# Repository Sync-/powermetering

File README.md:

# powermetering
```
ADE9000 application circuit based power meter
default ip: 192.168.178.204
st-flash --reset write build/powermetering.bin 0x08020000
```

Building:
```
cd software/website
./makefsdata
./copy.sh

cd software/powermetering
make
```

Flashing:
```
socat TCP:192.168.178.204:2000 build/powermetering.bin
```

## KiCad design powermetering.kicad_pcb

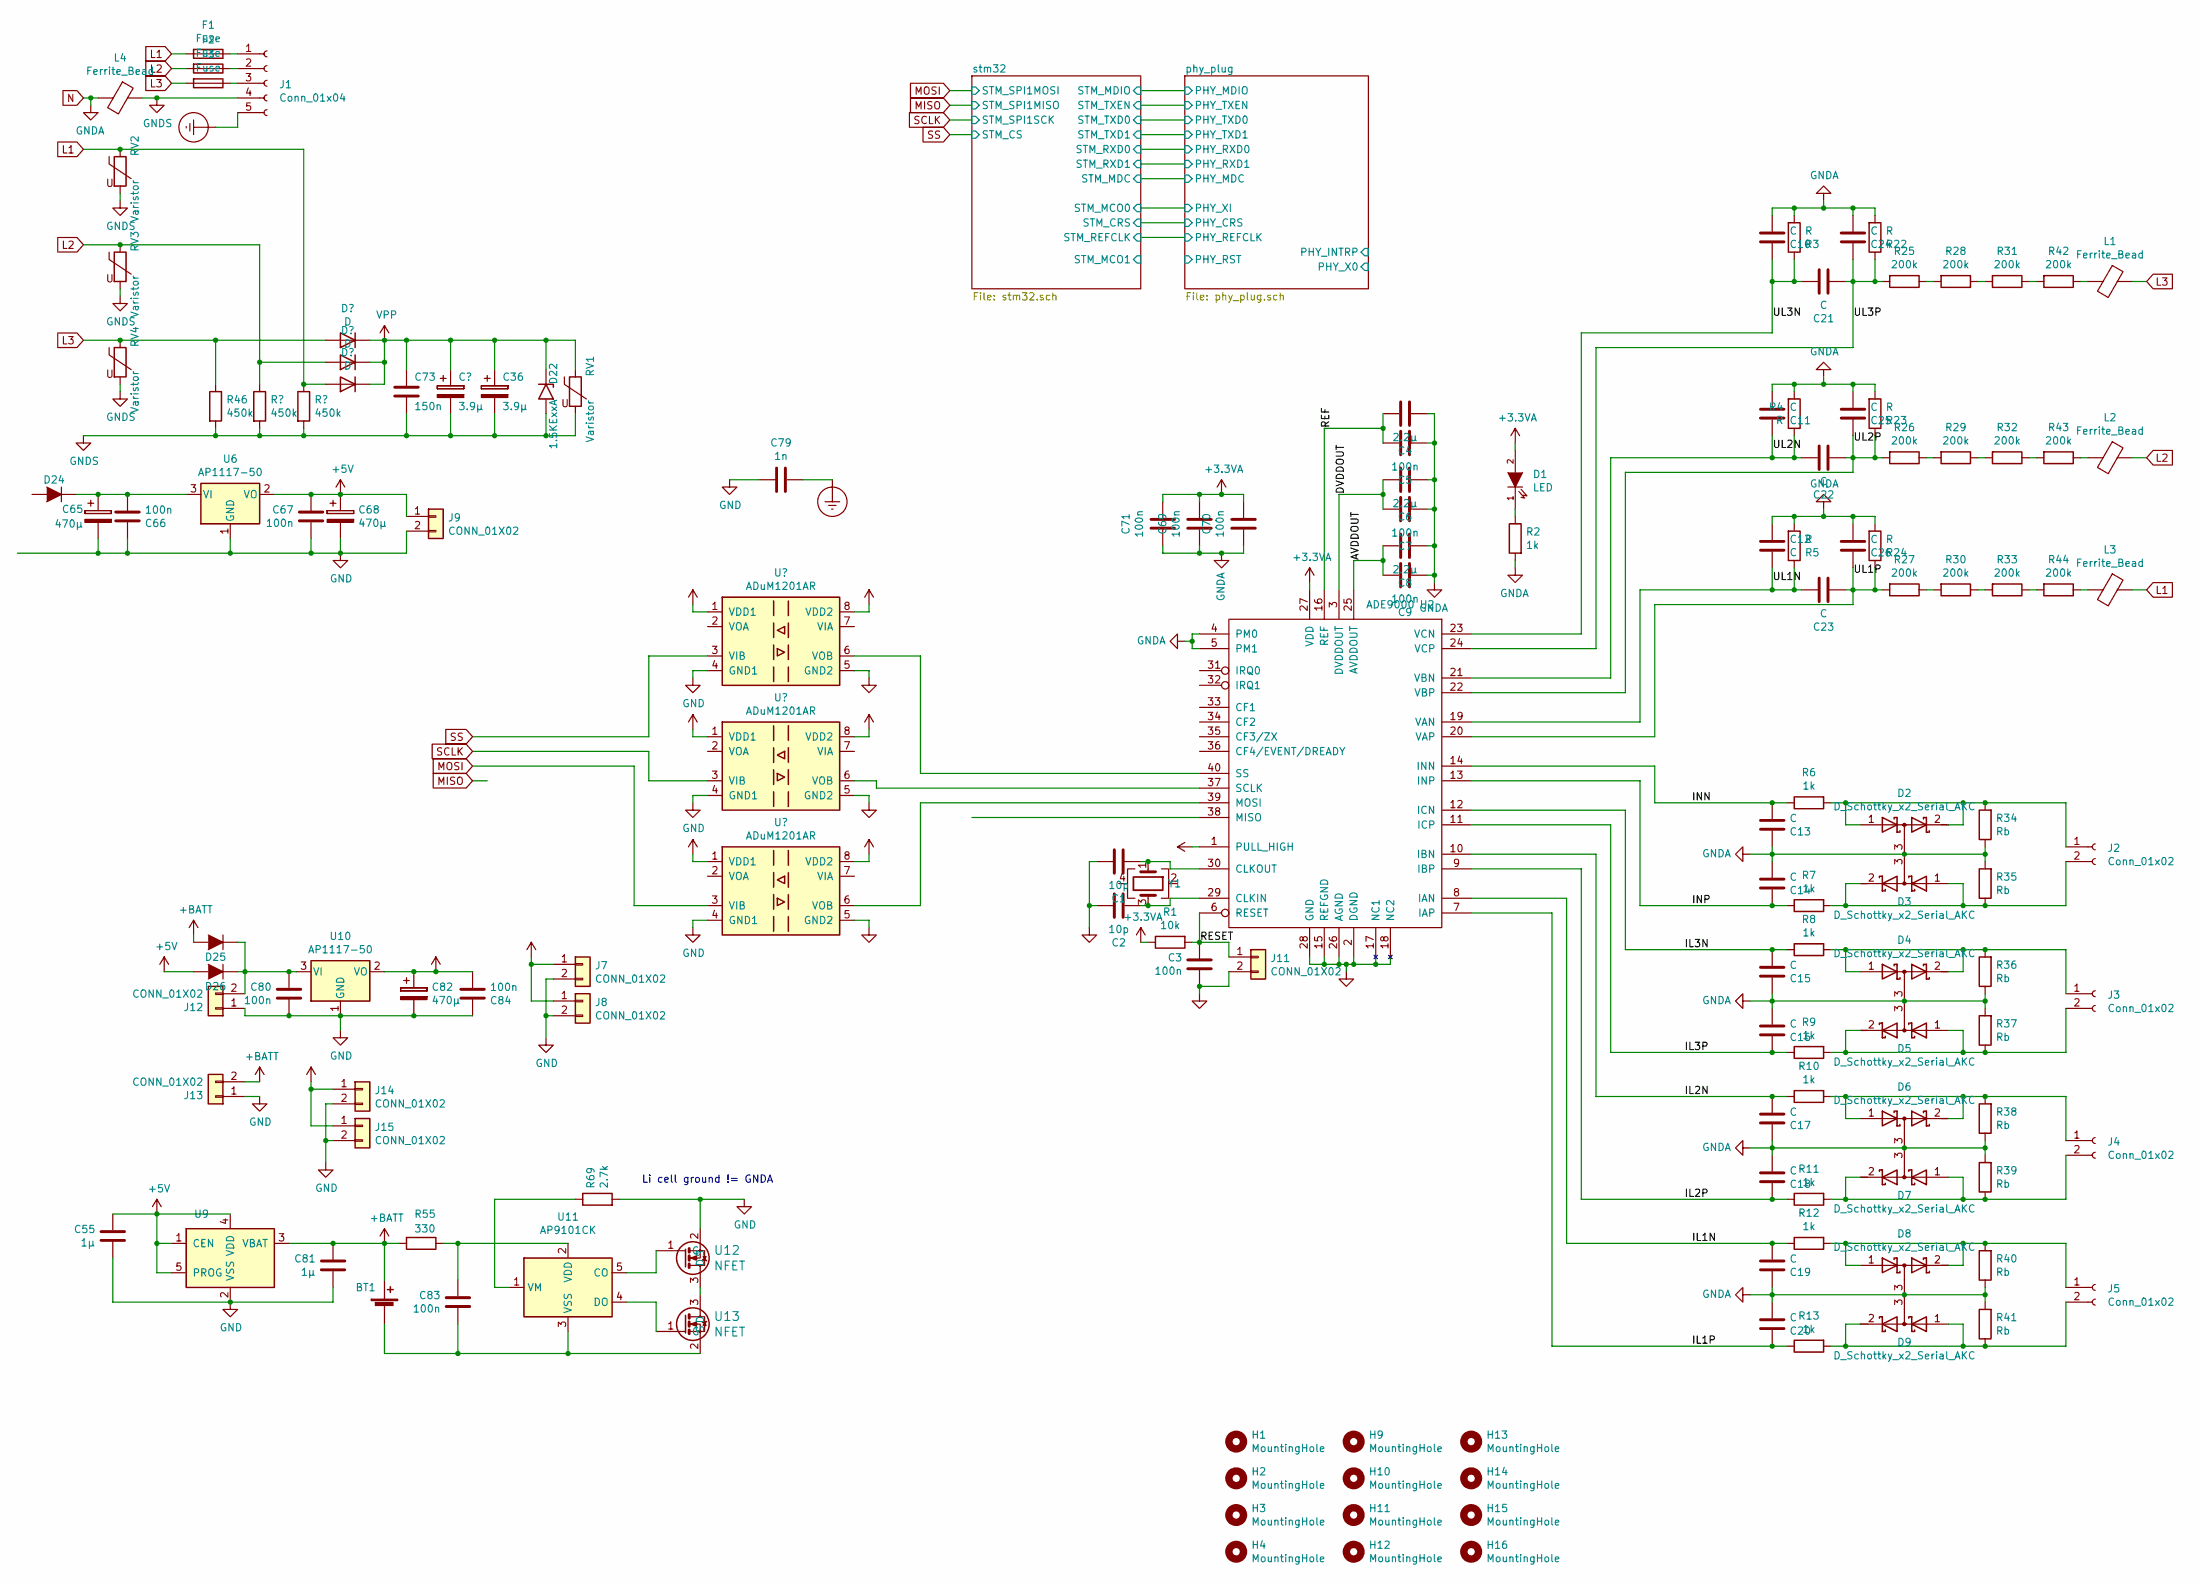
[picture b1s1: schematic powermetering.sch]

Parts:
BT1: Battery_Cell; 18650_keystone_54
C1, C2: 10p; C_0603
C3, C5, C7, C9, C69, C70, C71: 100n; C_0603
C4, C6, C8: 2.2µ; C_0603
C10, C11, C12, C13, C14, C15, C16, C17, C18, C19, C20, C21, C22, C23, C24, C25, C26: C; C_0603
C36: 3.9µ; CP_Elec_8x10
C55, C81: 1µ; C_0805
C65: 470µ; CP_Elec_8x10
C66, C67, C80, C83, C84: 100n; C_0805
C68, C82: 470µ; CP_Elec_8x10.5
C73: 150n; C_1808
C79: 1n; C_1806_4516Metric
D1: LED; LED-0805
D2, D3, D4, D5, D6, D7, D8, D9: D_Schottky_x2_Serial_AKC; SOT-23
D22: 1.5KExxA; D_SMC
D24, D25, D26: D; SMA_Standard
F1, F2, F3: Fuse; Fuse_SunFuse-6HP
H1, H2, H3, H4, H9, H10, H11, H12, H13, H14, H15, H16: MountingHole; MountingHole_5.5mm
J1: Conn_01x04; RM5.08_1x5_UP
J2, J3, J4, J5: Conn_01x02; RM5.08_1x2_UP
J7, J8, J9, J11, J12, J13, J14, J15: CONN_01X02; Pin_Header_Straight_1x02
L1, L2, L3, L4: Ferrite_Bead; C_0805
R1: 10k; R_0603
R2, R6, R7, R8, R9, R10, R11, R12, R13: 1k; R_0603
R3, R4, R5, R22, R23, R24: R; R_0603
R25, R26, R27, R28, R29, R30, R31, R32, R33, R42, R43, R44: 200k; R_1206
R34, R35, R36, R37, R38, R39, R40, R41: Rb; R_0612_1632Metric
R46: 450k; R_1206
R55: 330; R_0805
R69: 2.7k; R_0805
RV1, RV2, RV3, RV4: Varistor; RV_Disc_D12mm_W3.9mm_P7.5mm
U2: ADE9000; QFN-40-1EP_6x6mm_Pitch0.5mm
U6, U10: AP1117-50; SOT-223-3_TabPin2
U9: MCP73811T-420I-OT; SOT-23-5
U11: AP9101CK; SOT-23-5
U12, U13: NFET; SOT-23
Y1: Crystal; Crystal_SMD_3225-4Pin_3.2x2.5mm

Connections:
+3.3VA: C69.2, C70.2, C71.2, D1.2 (A), R1.1, U2.1 (PULL_HIGH), U2.27 (VDD); also elsewhere on the board
+3V3: C82.1, C84.2, J7.1, J8.1, J14.1, J15.1, U10.2 (VO); also elsewhere on the board
+5V: C55.1, C67.1, C68.1, D26.2 (A), J9.1, U6.2 (VO), U9.1 (CEN), U9.4 (VDD), U9.5 (PROG)
+BATT: BT1.1 (+), C81.1, D25.2 (A), J13.2, R55.2, U9.3 (VBAT)
/AVDDOUT: C8.2, C9.2, U2.25 (AVDDOUT)
/DVDDOUT: C6.2, C7.2, U2.3 (DVDDOUT)
/IL1N: C19.1, R12.1, U2.8 (IAN)
/IL1P: C20.2, R13.1, U2.7 (IAP)
/IL2N: C17.1, R10.1, U2.10 (IBN)
/IL2P: C18.2, R11.1, U2.9 (IBP)
/IL3N: C15.1, R8.1, U2.12 (ICN)
/IL3P: C16.2, R9.1, U2.11 (ICP)
/INN: C13.1, R6.1, U2.14 (INN)
/INP: C14.2, R7.1, U2.13 (INP)
/REF: C4.2, C5.2, U2.16 (REF)
/RESET: C3.2, J11.1, R1.2, U2.6 (RESET)
/UL1N: C12.2, C23.2, R5.1, U2.19 (VAN)
/UL1P: C23.1, C26.2, R24.1, R27.2, U2.20 (VAP)
/UL2N: C11.2, C22.2, R4.1, U2.21 (VBN)
/UL2P: C22.1, C25.2, R23.1, R26.2, U2.22 (VBP)
/UL3N: C10.2, C21.2, R3.1, U2.23 (VCN)
/UL3P: C21.1, C24.2, R22.1, R25.2, U2.24 (VCP)
Earth_Protective: C79.2, J1.5
GND: C55.2, C65.2, C66.1, C67.2, C68.2, C79.1, C80.2, C81.2, C82.2, C84.1, J7.2, J8.2, J9.2, J12.1, J13.1, J14.2, J15.2, R69.2, U6.1 (GND), U9.2 (VSS), U10.1 (GND), U12.2 (S); also elsewhere on the board
L1: F1.2, L3.1, RV2.1; also elsewhere on the board
L2: F2.2, L2.1, RV3.1; also elsewhere on the board
N: C1.2, C2.2, C3.1, C4.1, C5.1, C6.1, C7.1, C8.1, C9.1, C10.1, C11.1, C12.1, C13.2, C14.1, C15.2, C16.1, C17.2, C18.1, C19.2, C20.1, C24.1, C25.1, C26.1, C69.1, C70.1, C71.1, D2.3 (common), D3.3 (common), D4.3 (common), D5.3 (common), D6.3 (common), D7.3 (common), D8.3 (common), D9.3 (common), J11.2, L4.2, R2.2, R3.2, R4.2, R5.2, R22.2, R23.2, R24.2, R34.1, R35.2, R36.1, R37.2, R38.1, R39.2, R40.1, R41.2, U2.2 (DGND), U2.4 (PM0), U2.5 (PM1), U2.15 (REFGND), U2.17 (NC1), U2.18 (NC2), U2.26 (AGND), U2.28 (GND); also elsewhere on the board
unnamed: BT1.2 (-), C83.2, U11.3 (VSS), U13.2 (S)
unnamed: C1.1, U2.30 (CLKOUT), Y1.1
unnamed: C2.1, U2.29 (CLKIN), Y1.3
unnamed: C65.1, C66.2, D24.1 (K), U6.3 (VI)
unnamed: C80.1, D25.1 (K), D26.1 (K), J12.2, U10.3 (VI)
unnamed: C83.1, R55.1, U11.2 (VDD)
unnamed: D1.1 (K), R2.1
unnamed: D2.1 (A), D2.2 (K), J2.1, R6.2, R34.2
unnamed: D3.1 (A), D3.2 (K), J2.2, R7.2, R35.1
unnamed: D4.1 (A), D4.2 (K), J3.1, R8.2, R36.2
unnamed: D5.1 (A), D5.2 (K), J3.2, R9.2, R37.1
unnamed: D6.1 (A), D6.2 (K), J4.1, R10.2, R38.2
unnamed: D7.1 (A), D7.2 (K), J4.2, R11.2, R39.1
unnamed: D8.1 (A), D8.2 (K), J5.1, R12.2, R40.2
unnamed: D9.1 (A), D9.2 (K), J5.2, R13.2, R41.1
unnamed: F1.1, J1.1
unnamed: F2.1, J1.2
unnamed: F3.1, J1.3
unnamed: L1.2, R42.1
unnamed: L2.2, R43.1
unnamed: L3.2, R44.1
unnamed: R25.1, R28.2
unnamed: R26.1, R29.2
unnamed: R27.1, R30.2
unnamed: R28.1, R31.2
unnamed: R29.1, R32.2
unnamed: R30.1, R33.2
unnamed: R31.1, R42.2
unnamed: R32.1, R43.2
unnamed: R33.1, R44.2
unnamed: R69.1, U11.1 (VM)
unnamed 160: U2.37 (SCLK); also elsewhere on the board
unnamed 161: U2.38 (MISO); also elsewhere on the board
unnamed 162: U2.39 (MOSI); also elsewhere on the board
unnamed 163: U2.40 (SS); also elsewhere on the board
unnamed: U11.4 (DO), U13.1 (G)
unnamed: U11.5 (CO), U12.1 (G)
unnamed: U12.3 (D), U13.3 (D)

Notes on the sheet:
Li cell ground != GNDA

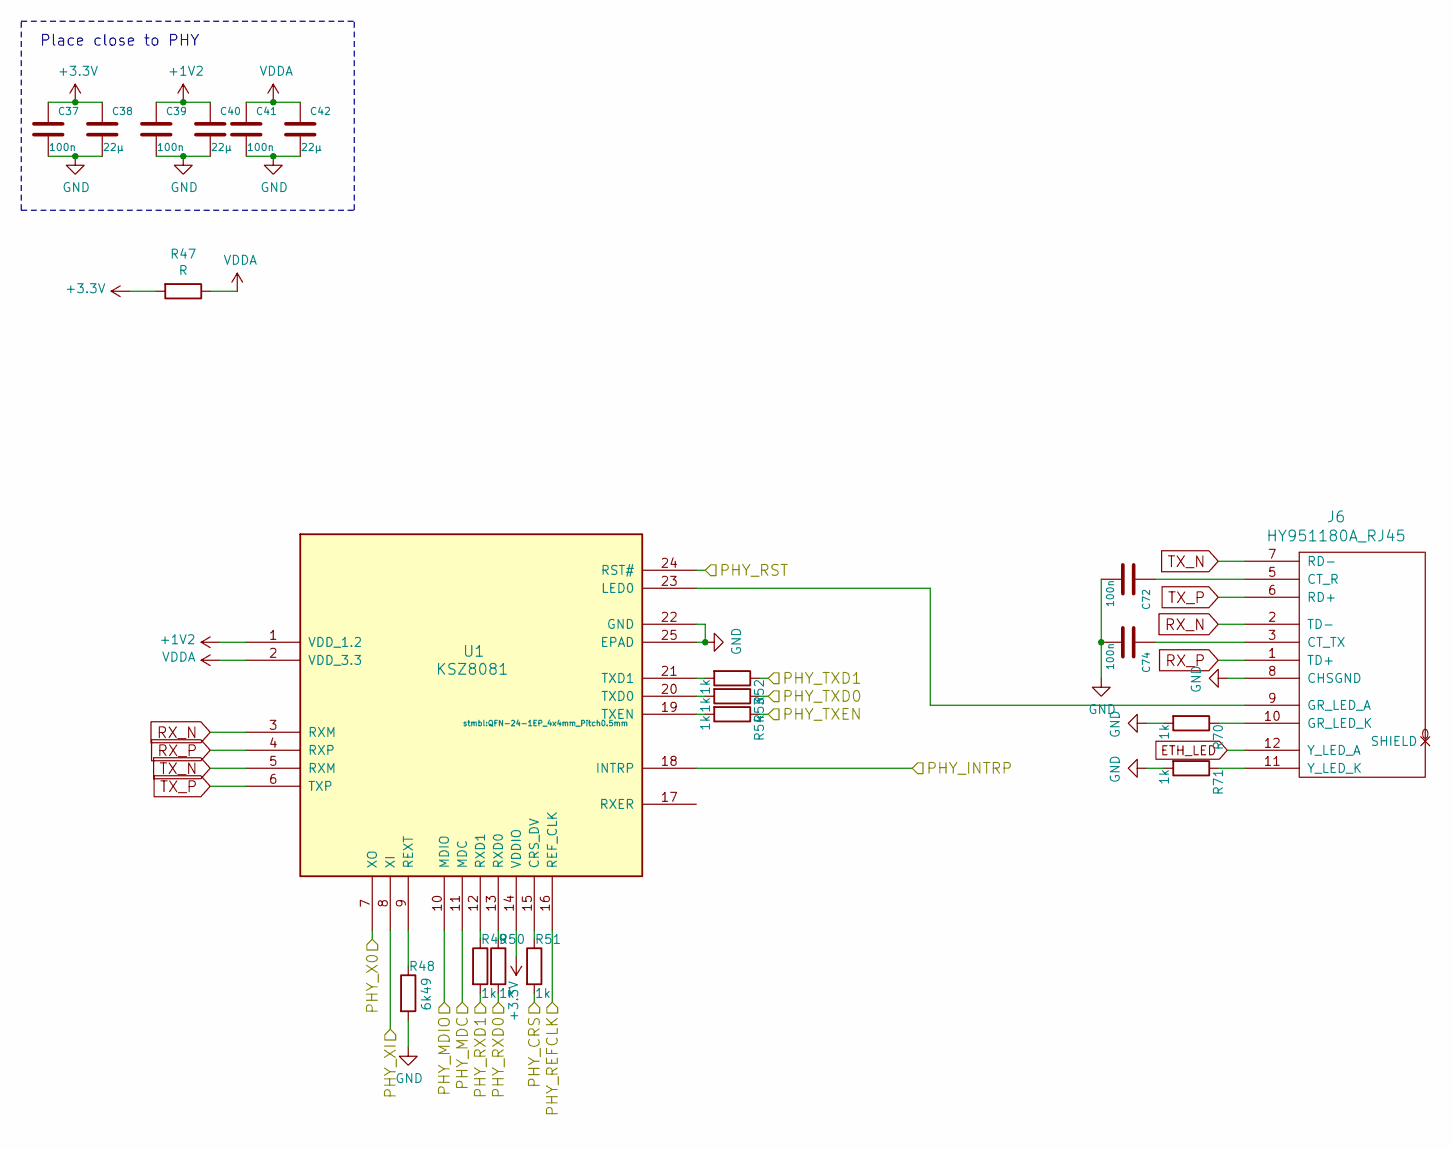
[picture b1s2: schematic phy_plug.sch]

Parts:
C37, C39, C41, C72, C74: 100n; C_0603
C38, C40, C42: 22µ; C_0805
J6: HY951180A_RJ45
R47: R; R_0603
R48: 6k49; R_0603
R49, R50, R51, R52, R53, R54, R70, R71: 1k; R_0603
U1: KSZ8081; QFN-24-1EP_4x4mm_Pitch0.5mm

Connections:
+1V2: C39.1, C40.1, U1.1 (VDD_1.2)
+3V3: C37.1, C38.1, R47.2, U1.14 (VDDIO); also elsewhere on the board
/PHY_CRS: R51.2; also elsewhere on the board
/PHY_INTRP: U1.18 (INTRP)
/PHY_MDIO: U1.10 (MDIO); also elsewhere on the board
/PHY_RST: U1.24 (RST#)
/PHY_TXD0: R53.1; also elsewhere on the board
/PHY_X0: U1.7 (XO)
/PHY_XI: U1.8 (XI); also elsewhere on the board
/STM_MDC: U1.11 (MDC); also elsewhere on the board
/STM_REFCLK: U1.16 (REF_CLK); also elsewhere on the board
/STM_RXD0: R50.2; also elsewhere on the board
/STM_RXD1: R49.2; also elsewhere on the board
/STM_TXD1: R52.1; also elsewhere on the board
/STM_TXEN: R54.1; also elsewhere on the board
ETH_LED: J6.12 (Y_LED_A); also elsewhere on the board
GND: C37.2, C38.2, C39.2, C40.2, C41.2, C42.2, C72.2, C74.2, J6.8 (CHSGND), R48.2, R70.2, R71.2, U1.22 (GND), U1.25 (EPAD); also elsewhere on the board
unnamed: C72.1, J6.5 (CT_R)
unnamed: C74.1, J6.3 (CT_TX)
unnamed: J6.9 (GR_LED_A), U1.23 (LED0)
unnamed: J6.10 (GR_LED_K), R70.1
unnamed: J6.11 (Y_LED_K), R71.1
unnamed: R48.1, U1.9 (REXT)
unnamed: R49.1, U1.12 (RXD1)
unnamed: R50.1, U1.13 (RXD0)
unnamed: R51.1, U1.15 (CRS_DV)
unnamed: R52.2, U1.21 (TXD1)
unnamed: R53.2, U1.20 (TXD0)
unnamed: R54.2, U1.19 (TXEN)
RX_N: J6.2 (TD-), U1.3 (RXM)
RX_P: J6.1 (TD+), U1.4 (RXP)
TX_N: J6.7 (RD-), U1.5 (RXM)
TX_P: J6.6 (RD+), U1.6 (TXP)
VDDA: C41.1, C42.1, R47.1, U1.2 (VDD_3.3)

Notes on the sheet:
Place close to PHY

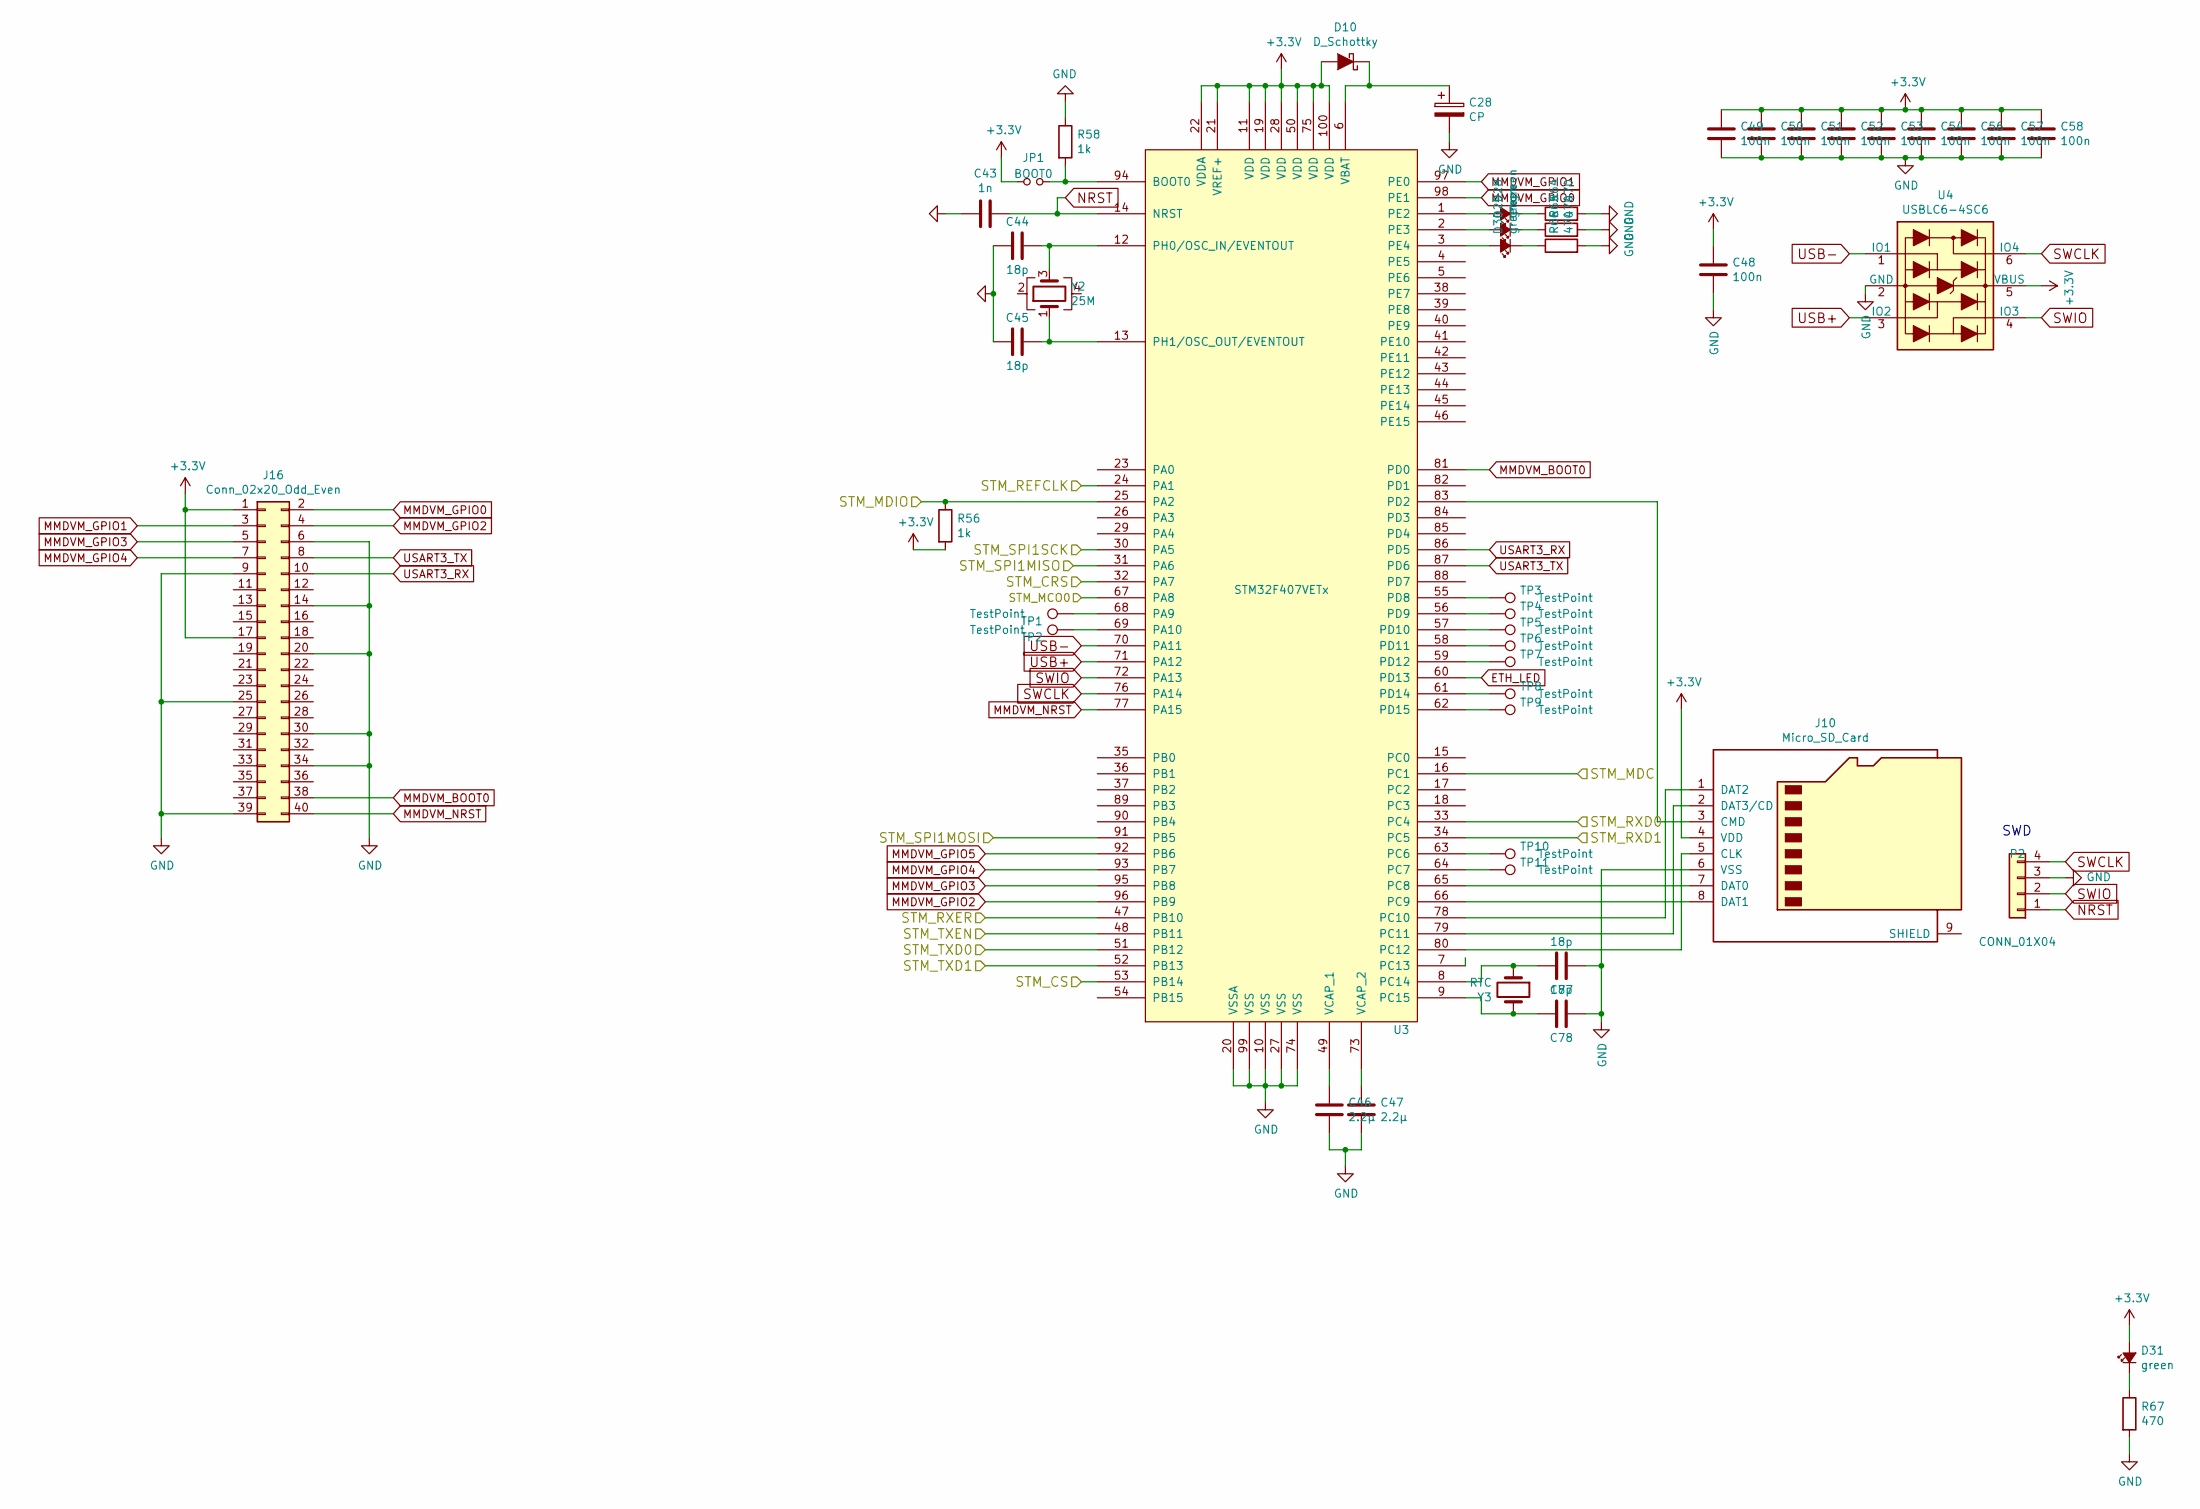
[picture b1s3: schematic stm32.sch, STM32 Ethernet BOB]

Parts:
C28: CP
C43: 1n; C_0603; Tolerance X5R; Voltage 50V
C44, C45, C77, C78: 18p; C_0603; Tolerance X5R; Voltage 50V
C46, C47: 2.2µ; C_0603; Tolerance X5R; Voltage 25V
C48, C49, C50, C51, C52, C53, C54, C56, C57, C58: 100n; C_0603; Tolerance X5R; Voltage 50V
D10: D_Schottky
D28, D29, D30, D31: green; LED-0805
J10: Micro_SD_Card; microSD_HC_Hirose_DM3BT-DSF-PEJS
J16: Conn_02x20_Odd_Even; PinHeader_2x20_P2.54mm_Vertical
JP1: BOOT0; SOLDER_JUMPER
P2: CONN_01X04; Pin_Header_Straight_1x04
R56, R58: 1k; R_0603; Tolerance 1%
R64, R65, R66, R67: 470; R_0603; Tolerance 1%
TP1, TP2, TP3, TP4, TP5, TP6, TP7, TP8, TP9, TP10, TP11: TestPoint; TestPoint_Pad_D1.0mm
U3: STM32F407VETx; LQFP-100_14x14mm_Pitch0.5mm
U4: USBLC6-4SC6; SOT-23-6
Y2: 25M; Crystal_SMD_3225-4Pin_3.2x2.5mm
Y3: RTC; Crystal_SMD_3215-2Pin_3.2x1.5mm

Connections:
+3V3: C48.2, C49.2, C50.2, C51.2, C52.2, C53.2, C54.2, C56.2, C57.2, C58.2, D10.2 (A), D31.2 (A), J10.4 (VDD), J16.1, J16.17, JP1.2, R56.2, U3.11 (VDD), U3.19 (VDD), U3.21 (VREF+), U3.22 (VDDA), U3.28 (VDD), U3.50 (VDD), U3.75 (VDD), U3.100 (VDD), U4.5 (VBUS); also elsewhere on the board
/PHY_CRS: U3.32 (PA7); also elsewhere on the board
/PHY_MDIO: R56.1, U3.25 (PA2); also elsewhere on the board
/PHY_TXD0: U3.51 (PB12); also elsewhere on the board
/PHY_XI: U3.67 (PA8); also elsewhere on the board
/STM_MDC: U3.16 (PC1); also elsewhere on the board
/STM_REFCLK: U3.24 (PA1); also elsewhere on the board
/STM_RXD0: U3.33 (PC4); also elsewhere on the board
/STM_RXD1: U3.34 (PC5); also elsewhere on the board
/STM_TXD1: U3.52 (PB13); also elsewhere on the board
/STM_TXEN: U3.48 (PB11); also elsewhere on the board
/stm32/STM_RXER: U3.47 (PB10)
ETH_LED: U3.60 (PD13); also elsewhere on the board
GND: C28.2, C43.2, C44.2, C45.2, C46.1, C47.1, C48.1, C49.1, C50.1, C51.1, C52.1, C53.1, C54.1, C56.1, C57.1, C58.1, C77.2, C78.2, J10.6 (VSS), J16.6, J16.9, J16.14, J16.20, J16.25, J16.30, J16.34, J16.39, P2.3, R58.1, R64.2, R65.2, R66.2, R67.2, U3.10 (VSS), U3.20 (VSSA), U3.27 (VSS), U3.74 (VSS), U3.99 (VSS), U4.2 (GND); also elsewhere on the board
MISO: U3.31 (PA6); also elsewhere on the board
MMDVM_BOOT0: J16.38, U3.81 (PD0)
MMDVM_GPIO0: J16.2, U3.98 (PE1)
MMDVM_GPIO1: J16.3, U3.97 (PE0)
MMDVM_GPIO2: J16.4, U3.96 (PB9)
MMDVM_GPIO3: J16.5, U3.95 (PB8)
MMDVM_GPIO4: J16.7, U3.93 (PB7)
MMDVM_GPIO5: U3.92 (PB6)
MMDVM_NRST: J16.40, U3.77 (PA15)
MOSI: U3.91 (PB5); also elsewhere on the board
NRST: C43.1, P2.1, U3.14 (NRST)
unnamed: C28.1, D10.1 (K), U3.6 (VBAT)
unnamed: C44.1, U3.12 (PH0/OSC_IN/EVENTOUT), Y2.3
unnamed: C45.1, U3.13 (PH1/OSC_OUT/EVENTOUT), Y2.1
unnamed: C46.2, U3.49 (VCAP_1)
unnamed: C47.2, U3.73 (VCAP_2)
unnamed: C77.1, U3.8 (PC14), Y3.1
unnamed: C78.1, U3.9 (PC15), Y3.2
unnamed: D28.1 (K), R64.1
unnamed: D28.2 (A), U3.1 (PE2)
unnamed: D29.1 (K), R65.1
unnamed: D29.2 (A), U3.2 (PE3)
unnamed: D30.1 (K), R66.1
unnamed: D30.2 (A), U3.3 (PE4)
unnamed: D31.1 (K), R67.1
unnamed: J10.1 (DAT2), U3.78 (PC10)
unnamed: J10.2 (DAT3/CD), U3.79 (PC11)
unnamed: J10.3 (CMD), U3.83 (PD2)
unnamed: J10.5 (CLK), U3.80 (PC12)
unnamed: J10.7 (DAT0), U3.65 (PC8)
unnamed: J10.8 (DAT1), U3.66 (PC9)
unnamed: JP1.1, R58.2, U3.94 (BOOT0)
unnamed: TP1.1, U3.68 (PA9)
unnamed: TP2.1, U3.69 (PA10)
unnamed: TP3.1, U3.55 (PD8)
unnamed: TP4.1, U3.56 (PD9)
unnamed: TP5.1, U3.57 (PD10)
unnamed: TP6.1, U3.58 (PD11)
unnamed: TP7.1, U3.59 (PD12)
unnamed: TP8.1, U3.61 (PD14)
unnamed: TP9.1, U3.62 (PD15)
unnamed: TP10.1, U3.63 (PC6)
unnamed: TP11.1, U3.64 (PC7)
SCLK: U3.30 (PA5); also elsewhere on the board
SS: U3.53 (PB14); also elsewhere on the board
SWCLK: P2.4, U3.76 (PA14), U4.6 (IO4)
SWIO: P2.2, U3.72 (PA13), U4.4 (IO3)
USART3_RX: J16.10, U3.86 (PD5)
USART3_TX: J16.8, U3.87 (PD6)
USB+: U3.71 (PA12), U4.3 (IO2)
USB-: U3.70 (PA11), U4.1 (IO1)

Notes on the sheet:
SWD

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
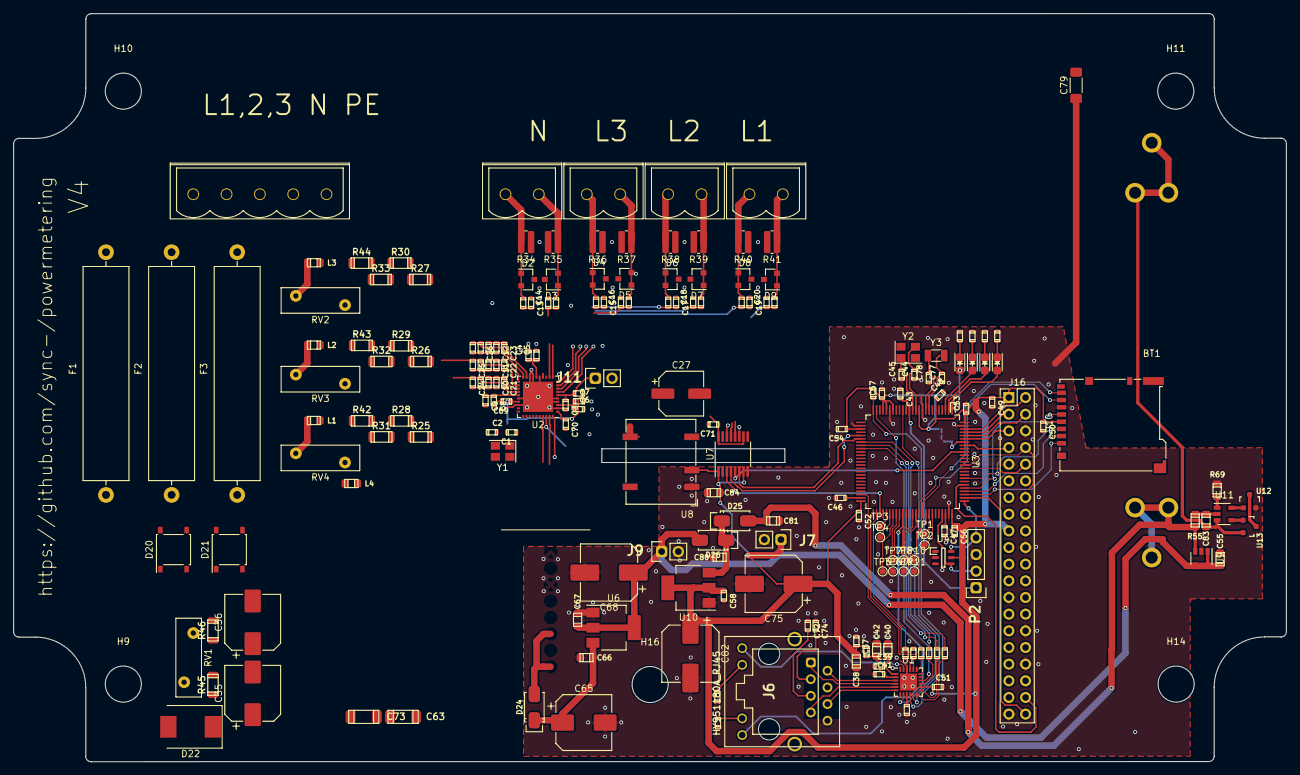
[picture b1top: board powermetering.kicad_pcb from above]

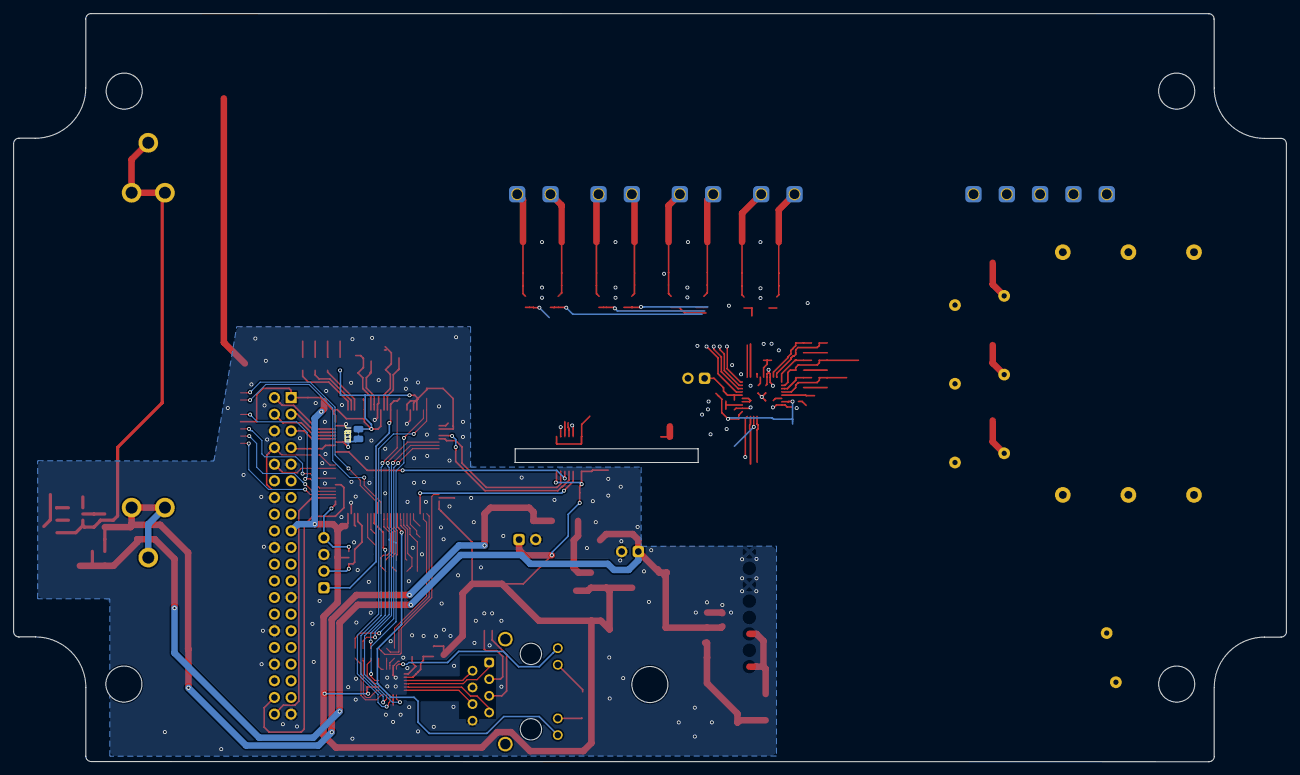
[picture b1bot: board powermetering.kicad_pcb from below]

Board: 2 copper layers, 194.0 x 114.1 mm, 200 parts (2 on the bottom side), 147 nets.

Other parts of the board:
C27: 470µ; CP_Elec_6.3x5.9
C35: 3.9µ; CP_Elec_8x10
C63: 150n; C_1808
C75: 470µ; CP_Elec_8x10.5
D20, D21: ABS10; Diode_Bridge_Diotec_ABS
R45: 450k; R_1206
U7: Si8641EB-B-IU; QSOP-16_3.9x4.9mm_P0.635mm
U8: NXE2S0505MC; Converter_DCDC_muRata_NXE2SxxxxMC_THT

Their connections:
+3.3VA: C27.1, U7.10, U7.16, U8.8; also elsewhere on the board
+3V3: C75.1, U7.1, U7.7, U8.3; also elsewhere on the board
GND: C75.2, U7.2, U7.8, U8.1; also elsewhere on the board
L1: D20.4; also elsewhere on the board
L2: D20.3; also elsewhere on the board
MISO: U7.6; also elsewhere on the board
MOSI: U7.5; also elsewhere on the board
N: C27.2, U7.9, U7.15, U8.7; also elsewhere on the board
unnamed 160: U7.13; also elsewhere on the board
unnamed 161: U7.11; also elsewhere on the board
unnamed 162: U7.12; also elsewhere on the board
unnamed 163: U7.14; also elsewhere on the board
SCLK: U7.4; also elsewhere on the board
SS: U7.3; also elsewhere on the board

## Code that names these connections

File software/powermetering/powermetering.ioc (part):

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Mcu.Name=STM32F407V(E-G)Tx
Mcu.Package=LQFP100
Mcu.UserName=STM32F407VGTx
PA1.Mode=RMII
PA1.Signal=ETH_REF_CLK
PA11.Mode=Device_Only
PA11.Signal=USB_OTG_FS_DM
PA12.Mode=Device_Only
PA12.Signal=USB_OTG_FS_DP
PA13.Mode=Serial_Wire
PA13.Signal=SYS_JTMS-SWDIO
PA14.Mode=Serial_Wire
PA14.Signal=SYS_JTCK-SWCLK
PA2.Mode=RMII
PA2.Signal=ETH_MDIO
PA5.Mode=Full_Duplex_Master
PA5.Signal=SPI1_SCK
PA6.Mode=Full_Duplex_Master
PA6.Signal=SPI1_MISO
PA7.Mode=RMII
PA7.Signal=ETH_CRS_DV
PA8.Mode=Clock-out-1
PA8.Signal=RCC_MCO_1
PB11.Mode=RMII
PB11.Signal=ETH_TX_EN
PB12.Mode=RMII
PB12.Signal=ETH_TXD0
PB13.Mode=RMII
PB13.Signal=ETH_TXD1
PB14.GPIOParameters=GPIO_Label
PB14.GPIO_Label=ADE_CS
PB14.Signal=GPIO_Output
PB5.Mode=Full_Duplex_Master
PB5.Signal=SPI1_MOSI
PB7.Signal=GPIO_Input
PB8.Mode=I2C
PB8.Signal=I2C1_SCL
PB9.Mode=I2C
PB9.Signal=I2C1_SDA
PC1.Mode=RMII
PC1.Signal=ETH_MDC
PC10.Mode=SD_4_bits_Wide_bus
PC10.Signal=SDIO_D2
PC11.Mode=SD_4_bits_Wide_bus
PC11.Signal=SDIO_D3
PC12.Mode=SD_4_bits_Wide_bus
PC12.Signal=SDIO_CK
PC14-OSC32_IN.Mode=LSE-External-Oscillator
PC14-OSC32_IN.Signal=RCC_OSC32_IN
PC15-OSC32_OUT.Mode=LSE-External-Oscillator
PC15-OSC32_OUT.Signal=RCC_OSC32_OUT
PC4.Mode=RMII
PC4.Signal=ETH_RXD0
PC5.Mode=RMII
PC5.Signal=ETH_RXD1
PC8.Mode=SD_4_bits_Wide_bus
PC8.Signal=SDIO_D0
PC9.Mode=SD_4_bits_Wide_bus
PC9.Signal=SDIO_D1
PD2.Mode=SD_4_bits_Wide_bus
PD2.Signal=SDIO_CMD
PD5.Mode=Asynchronous
PD5.Signal=USART2_TX
PD6.Mode=Asynchronous
PD6.Signal=USART2_RX
PE0.Signal=GPIO_Output
PE1.Signal=GPIO_Output
PE2.GPIOParameters=GPIO_Label
PE2.GPIO_Label=LED3
PE2.Signal=GPIO_Output
PE3.GPIOParameters=GPIO_Label
PE3.GPIO_Label=LED2
PE3.Signal=GPIO_Output
PE4.GPIOParameters=GPIO_Label
PE4.GPIO_Label=LED1
PE4.Signal=GPIO_Output
PH0-OSC_IN.Mode=HSE-External-Oscillator
PH0-OSC_IN.Signal=RCC_OSC_IN
PH1-OSC_OUT.Mode=HSE-External-Oscillator
PH1-OSC_OUT.Signal=RCC_OSC_OUT
RCC.HSE_VALUE=25000000
RCC.SYSCLKFreq_VALUE=168000000
RCC.SYSCLKSource=RCC_SYSCLKSOURCE_PLLCLK
board=custom

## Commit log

2019-01-04 first steps
2019-04-24 repair schematic, change pcb outline to spelsberg tk1111
2019-04-24 add cache lib
2019-04-24 correct xfmr pinout
2019-04-24 add stm32, ethernet phy, hv supply with lnk304
2019-04-25 remove xfmrs from top board, no space with 18650 backup battery
2019-04-25 start adding liion charger circuit
2019-04-27 add some 3d models
2019-04-28 Change to bigger housing
2019-05-16 add supply and AFE isolation
2019-05-16 eth phy
2019-05-17 finish routing of bottom board
2019-05-18 finalize proto board and add second board outline
2019-06-16 add software
2019-06-20 move fuses, add power header
2019-06-20 httpd works
2019-06-20 add fsdata.c + misc files
2019-06-24 displays voltage values through http
2019-06-24 reading stuff works
2019-06-25 V2 hardware
2019-06-25 still needs the V2 pinout
2019-06-25 swap phase order on current input
2019-07-03 small changes
2019-07-03 add EMI capacitor
2019-07-04 add sd card holder
2019-07-05 add bodge pads and move stuff around
2019-07-05 change ioc
2019-07-05 add ade reset jumper
2019-07-08 make it work™
2019-07-11 fix strange SPI issue ❓❗
2019-07-13 V2 works
2019-07-14 forgot some files
2019-07-14 generate mac from chipid
2019-07-14 gitignore
2019-07-14 add bootloader
2019-07-15 small production changes
2019-07-16 website stuff
2019-07-16 Update IOC
2019-07-16 current version
2019-07-16 add the rest of the HAL repo
2019-07-16 use different prios for the tasks
2019-07-17 influxdb client
2019-07-21 Change ADE registers to unsigned ints
2019-07-21 Fix 32bit write byte order
2019-07-21 Move ADE init and add calibration for the development unit
2019-07-21 Activate ssi again + small changes™
2019-07-25 fix bootloader
2019-07-25 move config to task
2019-08-31 fix SD card socket, move around psu stuff
2019-11-24 moved mqt to seperate file
2019-11-24 added us timer so vTaskGetRunTimeStats and vTaskList can be used, increased max tag insert len
2019-11-30 config interface
2019-11-30 influx config
2019-11-30 fix allowed chars in config string
2019-12-01 config foo
2019-12-01 favicon, name in title, name in config
2019-12-01 added get float
2019-12-01 fix mac irq overflow
2019-12-01 add network packet stats
2019-12-01 Remove stuff
2019-12-03 fix possible bug on config write and typo in frequency measurement
2019-12-04 add phasor diagram change ade data to 16bit low/high words add json to SSI files increase pbuf for ethernet
2019-12-05 fix json url, rename tasks, add free mem to status page
2019-12-05 add test.json
2019-12-05 add fsdata
2019-12-05 stackoverflow handler
2019-12-06 version info
2019-12-06 ignore pyc files
2019-12-06 remove pyc files
2019-12-06 oops
2019-12-06 limit amount of digits in data json and get fault current working
2019-12-06 add kicad lib tables
2019-12-06 add relative path in jdebug file + .gitignore
2019-12-06 modify rights on copy.sh
2019-12-06 add files to .gitignore
2019-12-06 Update main.c
    change as per review
2019-12-10 add flash stuff to readme
2019-12-10 fix stack sizes, fix malloc lock
2019-12-15 do not copy ccm to flash
2019-12-15 check if malloc locks can be overwritten
2019-12-16 removed usb, fatfs and tls
2019-12-16 added uptime
2019-12-16 change ethernetif from semaphore to task
2019-12-16 move json data to global var
2019-12-16 removed freertos.c, increased heap size
2019-12-23 change ade read to dma
2019-12-23 enable SYS_LIGHTWEIGHT_PROT increase buffer size add delay in read spi
2019-12-23 dummy read, lwip tcp core locking
2019-12-28 fix jlink file
2019-12-28 print ip on startup
2019-12-29 cleanup ade code
2019-12-29 add reset page, add cur_pri config option
2020-01-04 added power calculation
2020-01-04 Fixed S VA and Q VAR mapping
2020-01-04 Added Power values to influx
2020-01-22 remove eight pulse rectifier, add three pulse rectifier with artificial star point
2020-07-06 ade raw data, influx counter
2020-07-08 add calibration data to config
2020-07-08 read power factor from register
2021-02-07 use python3
2021-02-10 add auth to mqtt
2021-02-10 add mqtt support
2021-02-10 update debug
2021-02-11 make energy accumulation work....
2022-05-27 fix gcc10 support (extern hcrc, errno-include-foo)
2022-05-27 add dmr data transmit code
2022-05-28 add dmr config
2022-05-28 fix fs data scripts
2022-05-28 add dmr settings to generated filesystem
2022-05-28 fix git-ignores
2022-05-28 actually use config settings for DMR
2022-05-28 fix config parsing
2022-05-28 dmr: check dmr_en flag
2022-05-28 config: remove debug, init local variable
2022-05-28 dmr: add configurable waitstate
2022-05-28 dmr: remove obsolete usart code
2022-05-29 add dmr wait to config
2022-12-29 DHCP + Hostname funktioniert vielleicht
2023-08-16 reconfigure ade on config change, calculate calibration values
2023-08-16 Implement phase switch
2023-12-23 add cmake file
2023-12-23 update lwip
2023-12-23 update freertos
2023-12-23 fix code for new lwip and freertos version
2023-12-24 update hal and cmsis
2024-01-21 add dmb
2024-01-21 more dmb
2024-01-21 syscalls
2024-01-21 mqtt working
